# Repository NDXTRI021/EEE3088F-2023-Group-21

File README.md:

# EEE3088F-2023-Group-21
Project Repo for group 21 of EEE3088F (2023)

Instructions:
- Don't push to main if time sensitive. Push to your branch in case multiple people push at the same time.
- Try not to use zip files for push/pulls, they make it hard to figure out what's changed.
- Don't clutter main. Keep a good folder structure.

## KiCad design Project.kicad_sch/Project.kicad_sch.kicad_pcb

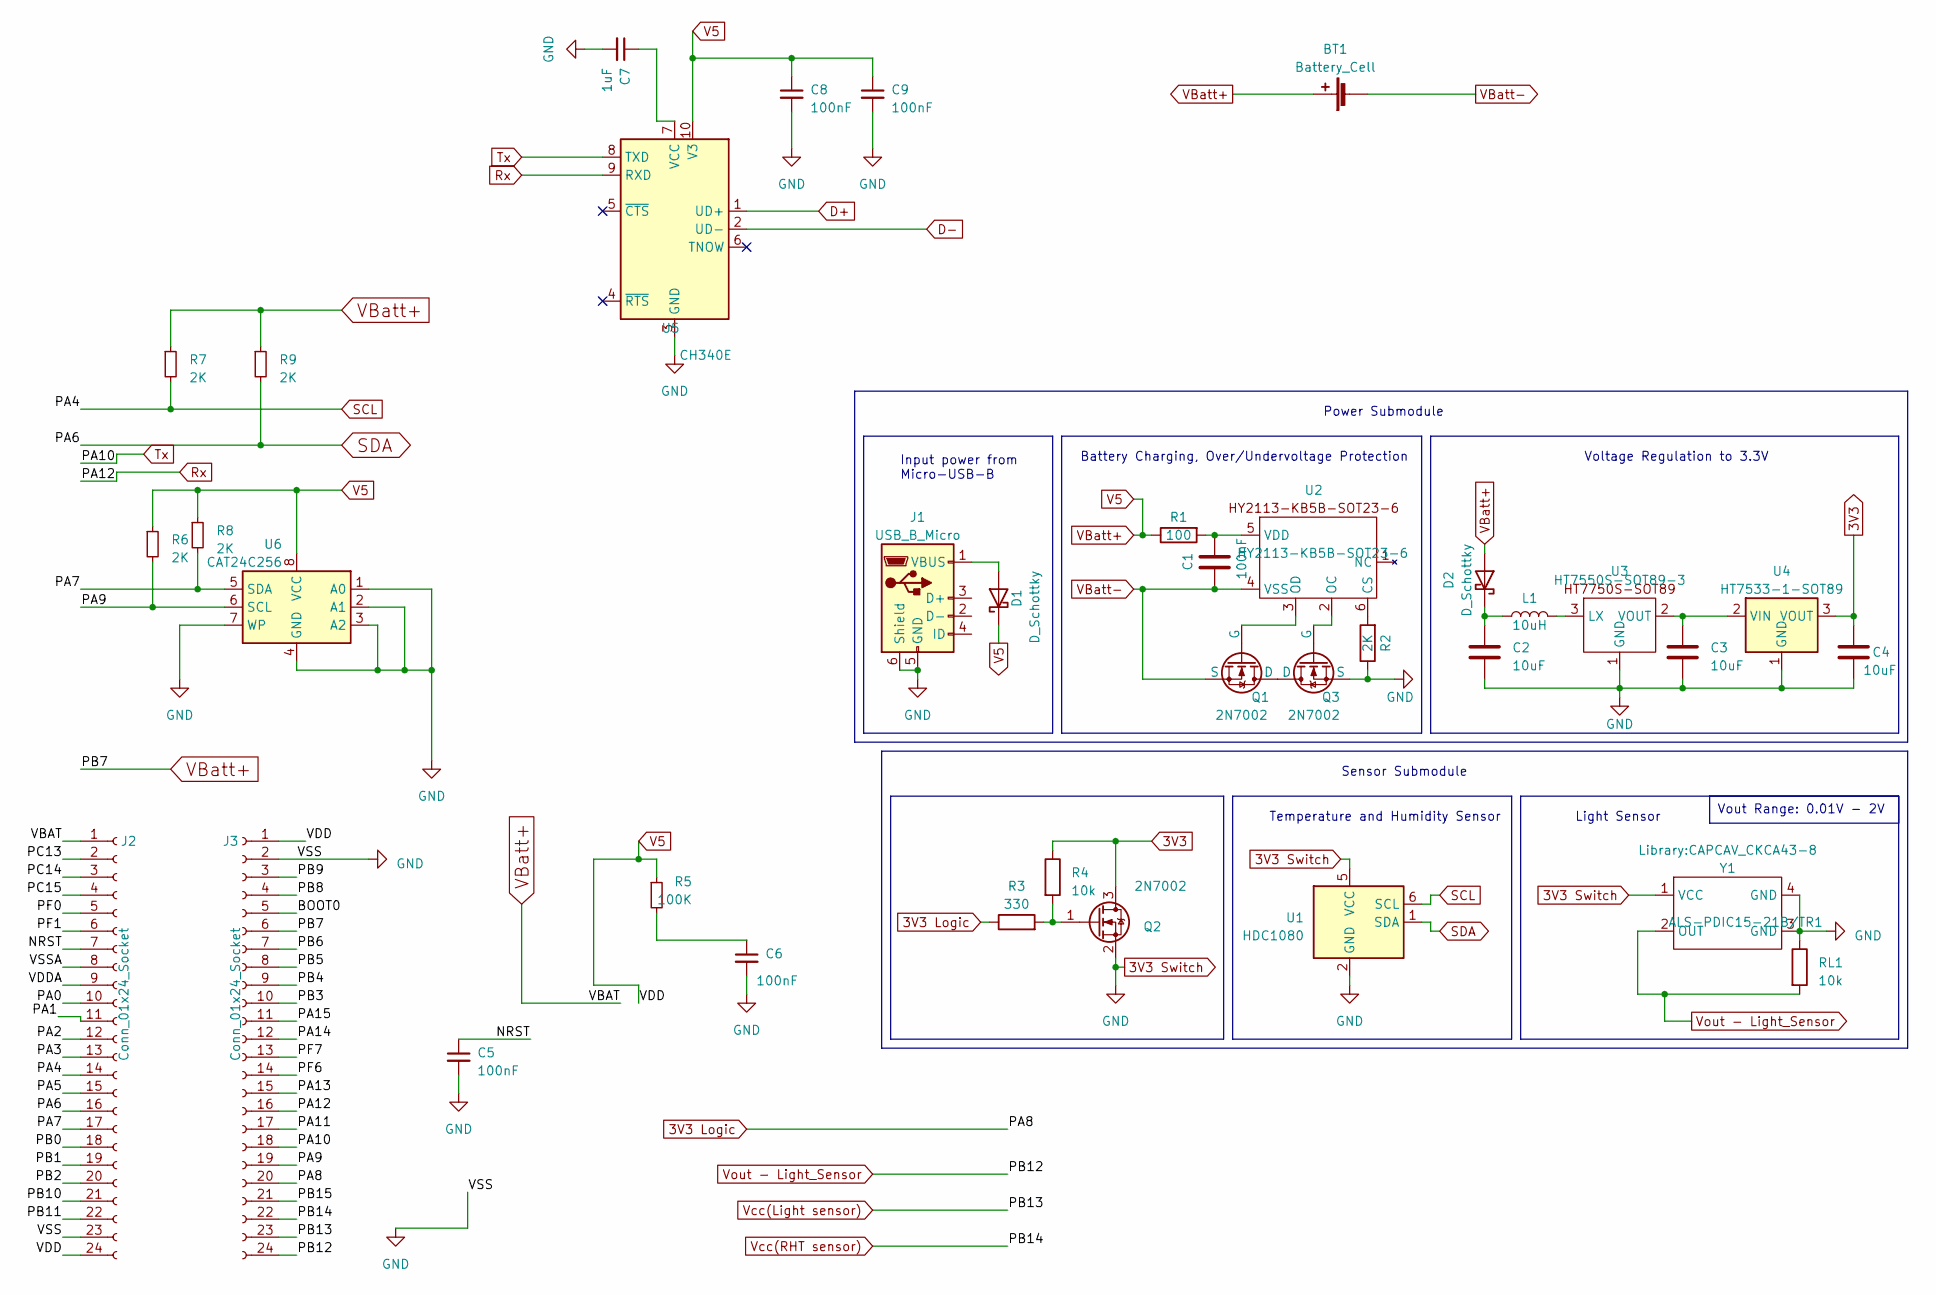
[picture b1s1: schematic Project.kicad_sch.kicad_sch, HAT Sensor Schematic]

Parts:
BT1: Battery_Cell; BAT_BH-18650-W
C1, C5, C6, C8, C9: 100nF; C_0603_1608Metric
C2, C3, C4: 10uF; C_0201_0603Metric
C7: 1uF; CP_EIA-1608-08_AVX-J
D1, D2: D_Schottky; D_SMA
J1: USB_B_Micro; SOT95P280X145-6N
J2, J3: Conn_01x24_Socket; PinSocket_1x24_P2.54mm_Vertical
L1: 10uH; L_1206_3216Metric
Q1, Q2, Q3: 2N7002; SOT-23
R1: 100; R_1206_3216Metric
R2, R6, R7, R8, R9: 2K; R_0402_1005Metric
R3: 330; R_0805_2012Metric
R4: 10k; R_0603_1608Metric
R5: 100K; R_0603_1608Metric
RL1: 10k; R_0603_1608Metric
U1: HDC1080; Texas_PWSON-N6
U2: HY2113-KB5B-SOT23-6; SOT-23-6
U3: HT7550S-SOT89-3; SOT-89-3
U4: HT7533-1-SOT89; SOT-89-3
U5: CH340E; MSOP-10_3x3mm_P0.5mm
U6: CAT24C256; SOIC-8W_5.3x5.3mm_P1.27mm
Y1: ALS-PDIC15-21B/TR1; CAPCAV_CKCA43-8

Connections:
3V3: C4.1, Q2.3 (D), R4.1, U4.3 (VOUT)
3V3 Logic: J3.20, R3.1
3V3 Switch: C2.2, C3.2, C4.2, C5.2, C6.2, C7.2, C8.2, C9.2, J1.5 (GND), J1.6 (Shield), J2.23, J3.2, Q2.2 (S), Q3.3 (S), R2.1, RL1.1, U1.2 (GND), U1.5 (VCC), U3.1 (GND), U4.1 (GND), U5.3 (GND), U6.1 (A0), U6.2 (A1), U6.3 (A2), U6.4 (GND), U6.7 (WP), Y1.1 (VCC), Y1.3 (GND), Y1.4 (GND)
/BOOT0: J3.5
/NRST: C5.1, J2.7
/PA0: J2.10
/PA1: J2.11
/PA2: J2.12
/PA3: J2.13
/PA5: J2.15
/PA7: J2.17, R8.2, U6.5 (SDA)
/PA9: J3.19, R6.2, U6.6 (SCL)
/PA11: J3.17
/PA13: J3.15
/PA14: J3.12
/PA15: J3.11
/PB0: J2.18
/PB1: J2.19
/PB2: J2.20
/PB3: J3.10
/PB4: J3.9
/PB5: J3.8
/PB6: J3.7
/PB8: J3.4
/PB9: J3.3
/PB10: J2.21
/PB11: J2.22
/PB15: J3.21
/PC13: J2.2
/PC14: J2.3
/PC15: J2.4
/PF0: J2.5
/PF1: J2.6
/PF6: J3.14
/PF7: J3.13
/VDDA: J2.9
/VSSA: J2.8
D+: U5.1 (UD+)
D-: U5.2 (UD-)
unnamed: C6.1, R5.2
unnamed: D1.2 (A), J1.1 (VBUS)
unnamed: C2.1, D2.1 (K), L1.2
unnamed: Q1.1 (D), Q3.1 (D)
unnamed: Q1.2 (G), U2.3 (OD)
unnamed: Q2.1 (G), R3.2, R4.2
unnamed: Q3.2 (G), U2.2 (OC)
unnamed: R2.2, U2.6 (CS)
unnamed: C1.1, R1.2, U2.5 (VDD)
unnamed: L1.1, U3.3 (LX)
unnamed: C3.1, U3.2 (VOUT), U4.2 (VIN)
unnamed: C7.1, U5.7 (VCC)
Rx: J3.16, U5.9 (RXD)
SCL: J2.14, R7.2, U1.6 (SCL)
SDA: J2.16, R9.2, U1.1 (SDA)
Tx: J3.18, U5.8 (TXD)
V5: BT1.1 (+), C8.1, C9.1, D1.1 (K), D2.2 (A), J2.1, J2.24, J3.1, J3.6, R1.1, R5.1, R6.1, R7.1, R8.1, R9.1, U5.10 (V3), U6.8 (VCC)
VBatt-: BT1.2 (-), C1.2, Q1.3 (S), U2.4 (VSS)
Vcc(Light sensor): J3.23
Vcc(RHT sensor): J3.22
Vout - Light_Sensor: J3.24, RL1.2, Y1.2 (OUT)

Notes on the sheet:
Vout Range: 0.01V - 2V
Temperature and Humidity Sensor
Power Submodule
Battery Charging, Over/Undervoltage Protection
Voltage Regulation to 3.3V
Sensor Submodule
Light Sensor
Input power from Micro-USB-B

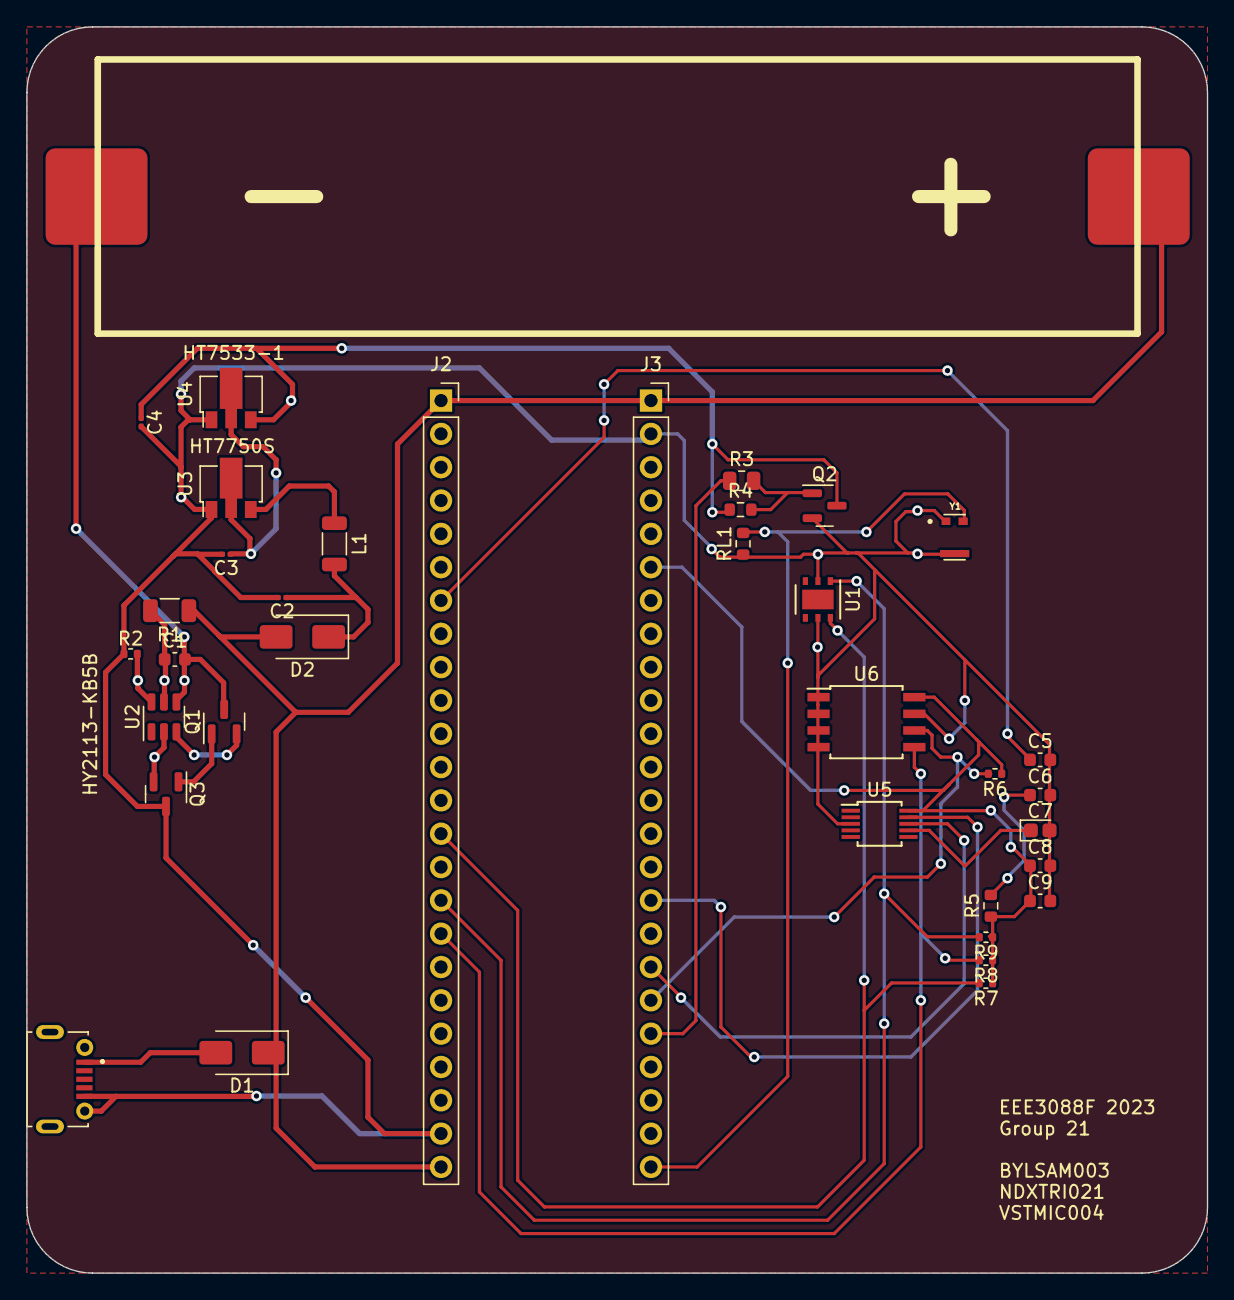
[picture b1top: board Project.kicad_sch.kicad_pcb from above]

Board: 2 copper layers, 90.0 x 95.0 mm, 36 parts (0 on the bottom side), 25 nets.

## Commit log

2023-02-27 Create Timeline and To-Do
2023-03-06 Add files via upload
    Draft bill of materials for the sensors. Excluding push buttons or any other power regulators/interfacing components.
2023-03-07 Add files via upload
    Microcontroller draft Bill of Material
2023-03-09 Refactoring
2023-03-09 Rename Total BOM.md to total_draftBOM.md
2023-03-20 Changed draft BOM to a Sheets doc
2023-03-20 Deleted BOM.xlsx. Find draft BOM under DraftBom folder
2023-03-21 duplicate
2023-03-21 Update: Trishane
2023-03-21 Fixed labels and voltage on Switch
2023-03-21 Create Microcontroller Schematic
2023-03-21 Combined BOM updated, in CSV format
2023-04-14 Gerbers Final
2023-04-14 PCB Final
2023-04-14 Create a
2023-04-14 Rename KiCad Files/a to Project.kicad_sch/a
2023-04-14 Uploaded project files, not as a zip this time
    Easier to work with, but not like we need it anymore so...
